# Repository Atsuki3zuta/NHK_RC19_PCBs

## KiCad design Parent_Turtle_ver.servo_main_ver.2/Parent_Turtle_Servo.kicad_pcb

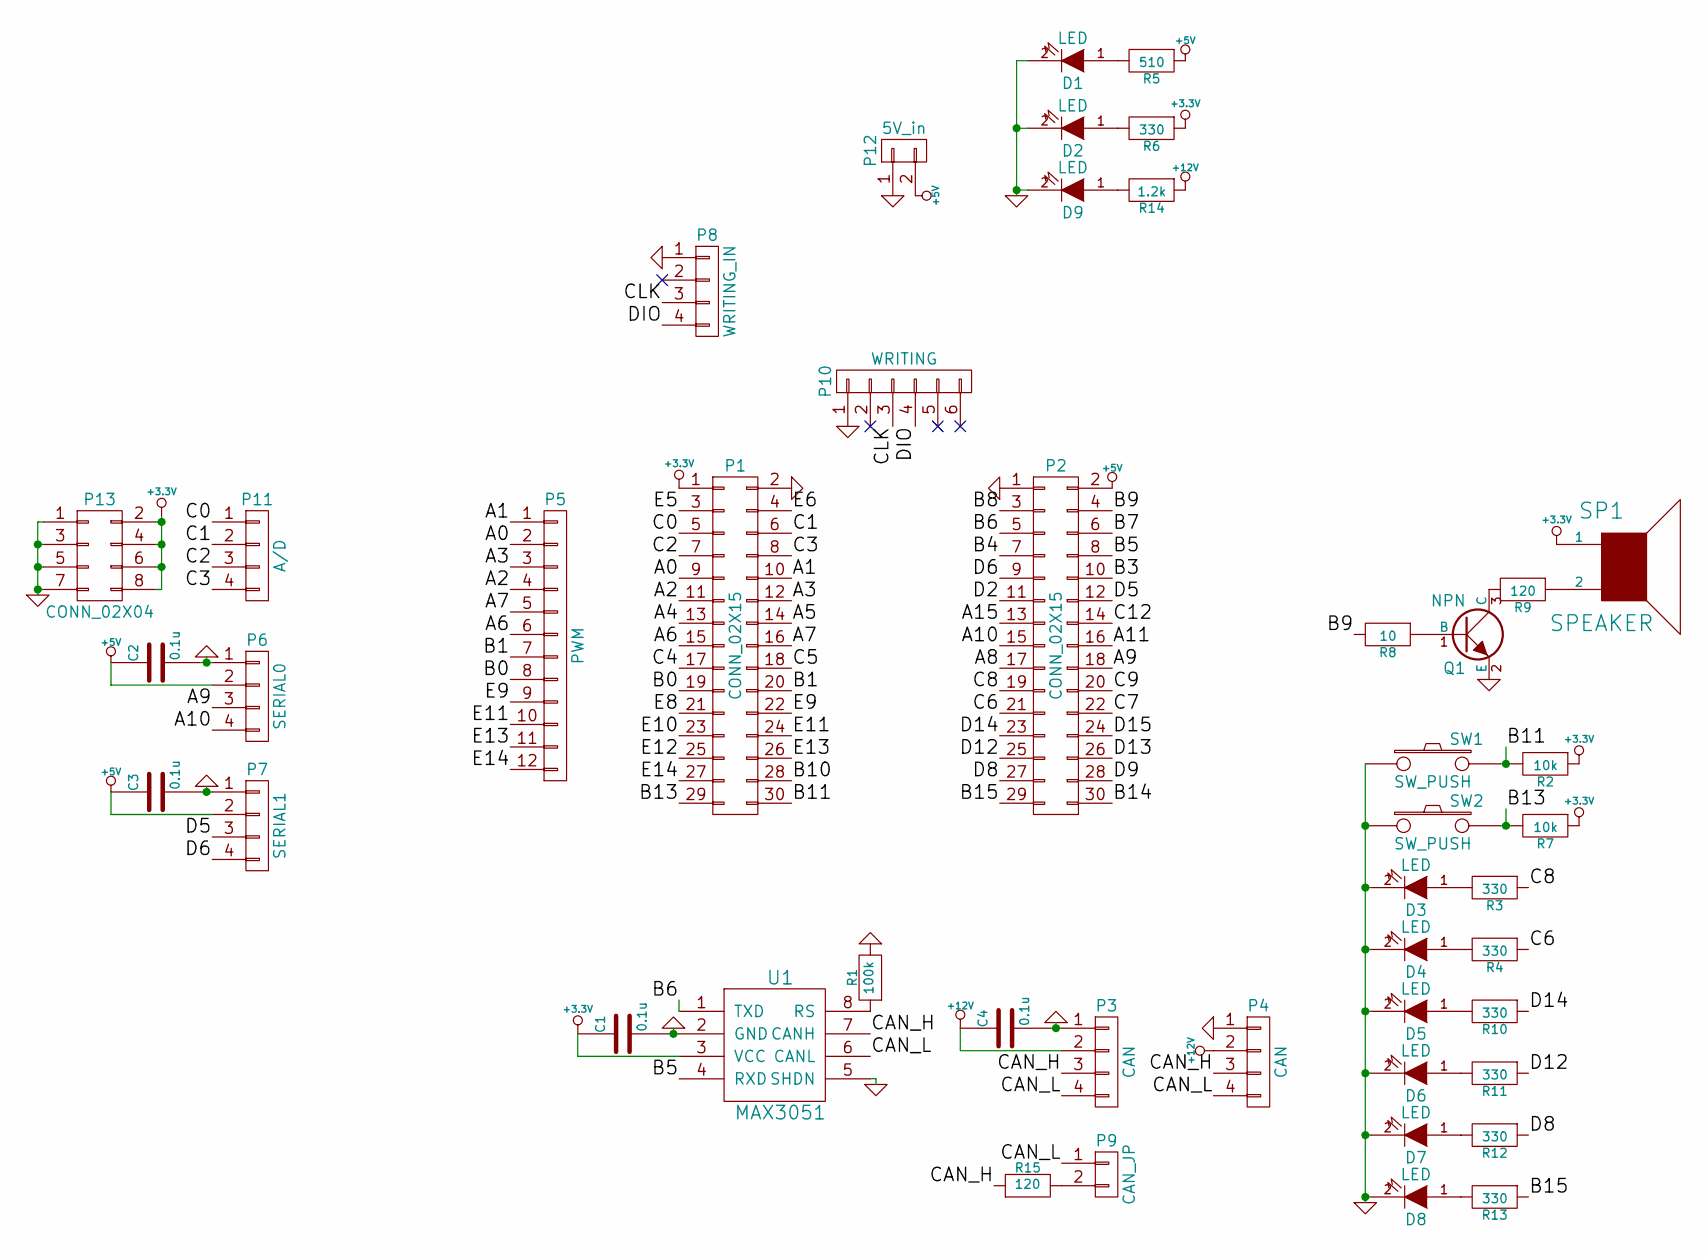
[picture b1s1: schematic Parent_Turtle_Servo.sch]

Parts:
C1, C2, C3, C4: 0.1u; C_0603
D1, D2, D3, D4, D5, D6, D7, D8, D9: LED; LED-3MM
P1, P2: CONN_02X15; Socket_Strip_Straight_2x15
P3: CAN; XA_4T
P4: CAN; XA_4LC
P5: PWM; Pin_Header_Straight_1x12
P6: SERIAL0; XA_4T
P7: SERIAL1; XA_4T
P8: WRITING_IN; XA_4LC
P9: CAN_JP; Pin_Header_Straight_1x02
P10: WRITING; Socket_Strip_Straight_1x06
P11: A/D; Pin_Header_Straight_1x04
P12: 5V_in; XA_2T
P13: CONN_02X04; Pin_Header_Straight_2x04
Q1: NPN; SOT-23
R1: 100k; R_0603
R2, R7: 10k; R_0603
R3, R4, R6, R10, R11, R12, R13: 330; R_0603
R5: 510; R_0603
R8: 10; R_0603
R9, R15: 120; R_0603
R14: 1.2k; R_0603
SP1: SPEAKER; UGCT7525AN4
SW1, SW2: SW_PUSH; SW_PUSH_6mm
U1: MAX3051; SOIC-8_3.9x4.9mm_Pitch1.27mm

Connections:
+3.3V: C1.1, P1.1, P13.2, P13.4, P13.6, P13.8, R2.1, R6.1, R7.1, SP1.1, U1.3 (VCC)
+5V: C2.1, C3.1, P2.2, P6.2, P7.2, P12.2, R5.1
+12V: C4.1, P3.2, P4.2, R14.1
/A0: P1.9, P5.2
/A1: P1.10, P5.1
/A2: P1.11, P5.4
/A3: P1.12, P5.3
/A4: P1.13
/A5: P1.14
/A6: P1.15, P5.6
/A7: P1.16, P5.5
/A8: P2.17
/A9: P2.18, P6.3
/A10: P2.15, P6.4
/A11: P2.16
/A15: P2.13
/B0: P1.19, P5.8
/B1: P1.20, P5.7
/B3: P2.10
/B4: P2.7
/B5: P2.8, U1.4 (RXD)
/B6: P2.5, U1.1 (TXD)
/B7: P2.6
/B8: P2.3
/B9: P2.4, R8.2
/B10: P1.28
/B11: P1.30, R2.2, SW1.2
/B13: P1.29, R7.2, SW2.2
/B14: P2.30
/B15: P2.29, R13.1
/C0: P1.5, P11.1
/C1: P1.6, P11.2
/C2: P1.7, P11.3
/C3: P1.8, P11.4
/C4: P1.17
/C5: P1.18
/C6: P2.21, R4.1
/C7: P2.22
/C8: P2.19, R3.1
/C9: P2.20
/C12: P2.14
/CAN_H: P3.3, P4.3, R15.1, U1.7 (CANH)
/CAN_L: P3.4, P4.4, P9.1, U1.6 (CANL)
/CLK: P8.3, P10.3
/D2: P2.11
/D5: P2.12, P7.3
/D6: P2.9, P7.4
/D8: P2.27, R12.1
/D9: P2.28
/D12: P2.25, R11.1
/D13: P2.26
/D14: P2.23, R10.1
/D15: P2.24
/DIO: P8.4, P10.4
/E5: P1.3
/E6: P1.4
/E8: P1.21
/E9: P1.22, P5.9
/E10: P1.23
/E11: P1.24, P5.10
/E12: P1.25
/E13: P1.26, P5.11
/E14: P1.27, P5.12
GND: C1.2, C2.2, C3.2, C4.2, D1.2 (K), D2.2 (K), D3.2 (K), D4.2 (K), D5.2 (K), D6.2 (K), D7.2 (K), D8.2 (K), D9.2 (K), P1.2, P2.1, P3.1, P4.1, P6.1, P7.1, P8.1, P10.1, P12.1, P13.1, P13.3, P13.5, P13.7, Q1.2 (E), R1.2, SW1.1, SW2.1, U1.2 (GND), U1.5 (SHDN)
unnamed: D1.1 (A), R5.2
unnamed: D2.1 (A), R6.2
unnamed: D3.1 (A), R3.2
unnamed: D4.1 (A), R4.2
unnamed: D5.1 (A), R10.2
unnamed: D6.1 (A), R11.2
unnamed: D7.1 (A), R12.2
unnamed: D8.1 (A), R13.2
unnamed: D9.1 (A), R14.2
unnamed: P9.2, R15.2
unnamed: Q1.1 (B), R8.1
unnamed: Q1.3 (C), R9.2
unnamed: R1.1, U1.8 (RS)
unnamed: R9.1, SP1.2

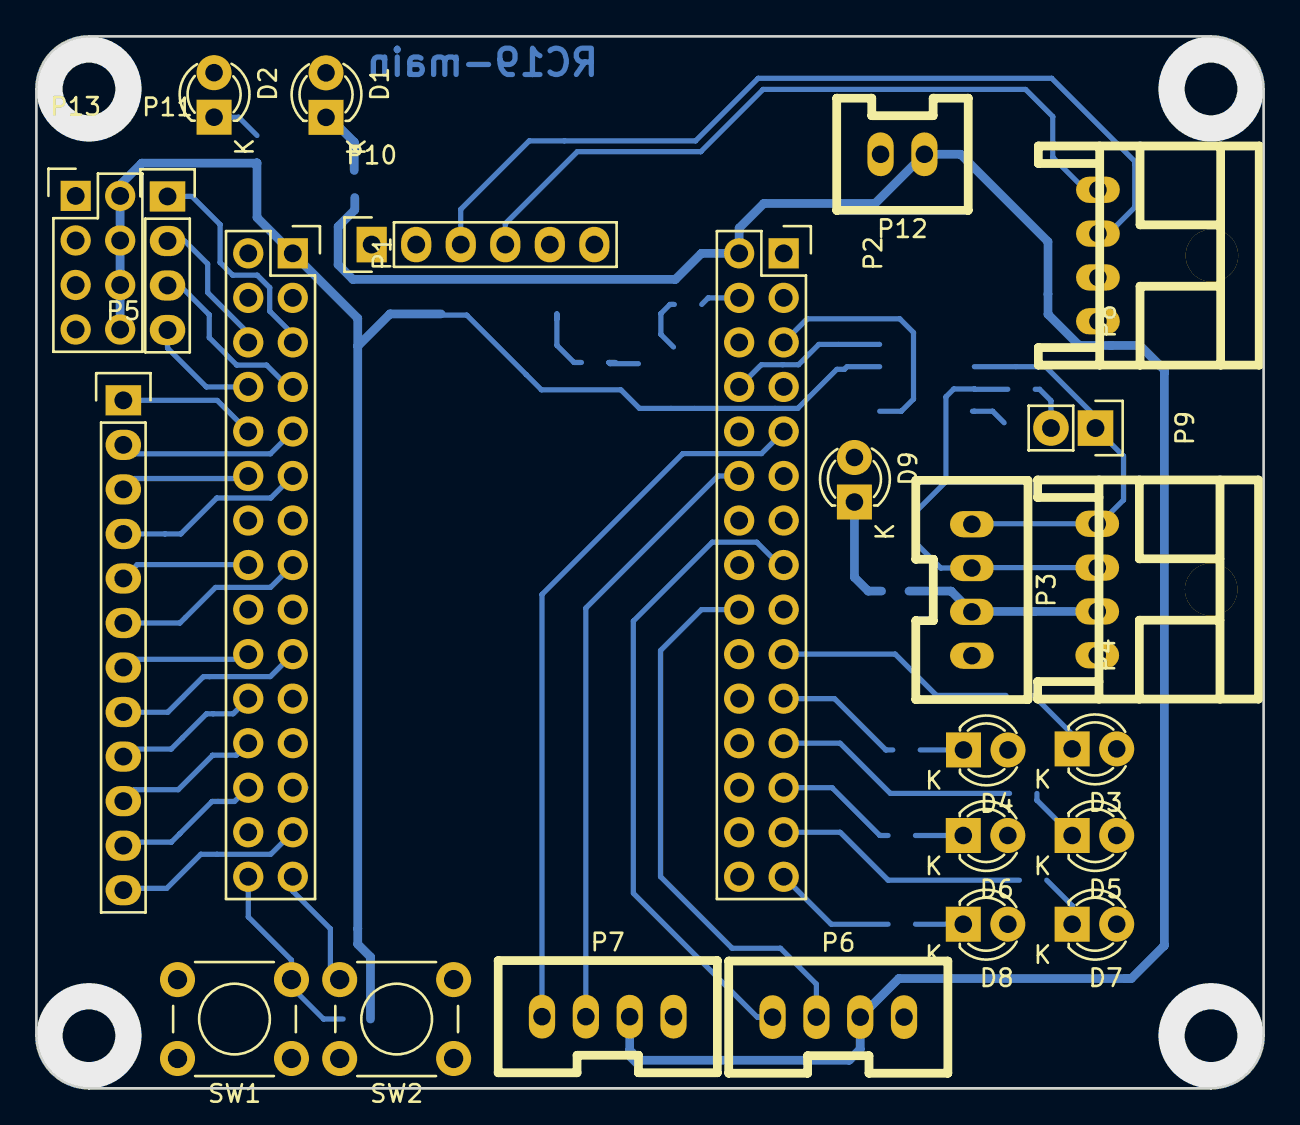
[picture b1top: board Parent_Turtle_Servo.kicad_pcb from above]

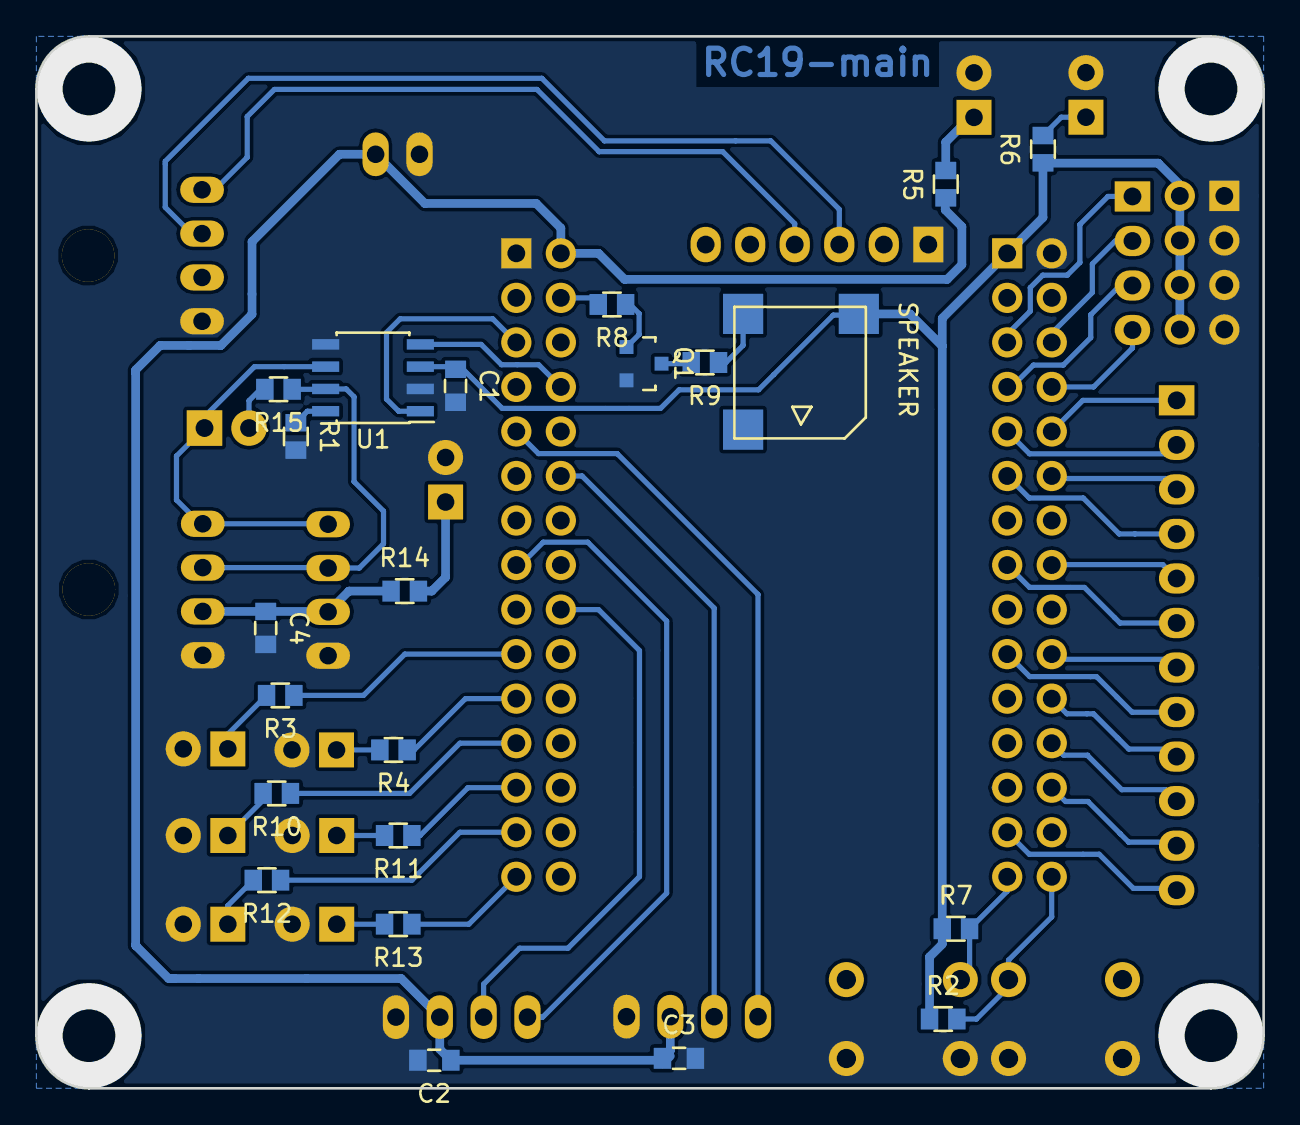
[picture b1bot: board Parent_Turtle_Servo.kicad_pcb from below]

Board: 2 copper layers, 70.0 x 60.0 mm, 46 parts (22 on the bottom side), 53 nets.

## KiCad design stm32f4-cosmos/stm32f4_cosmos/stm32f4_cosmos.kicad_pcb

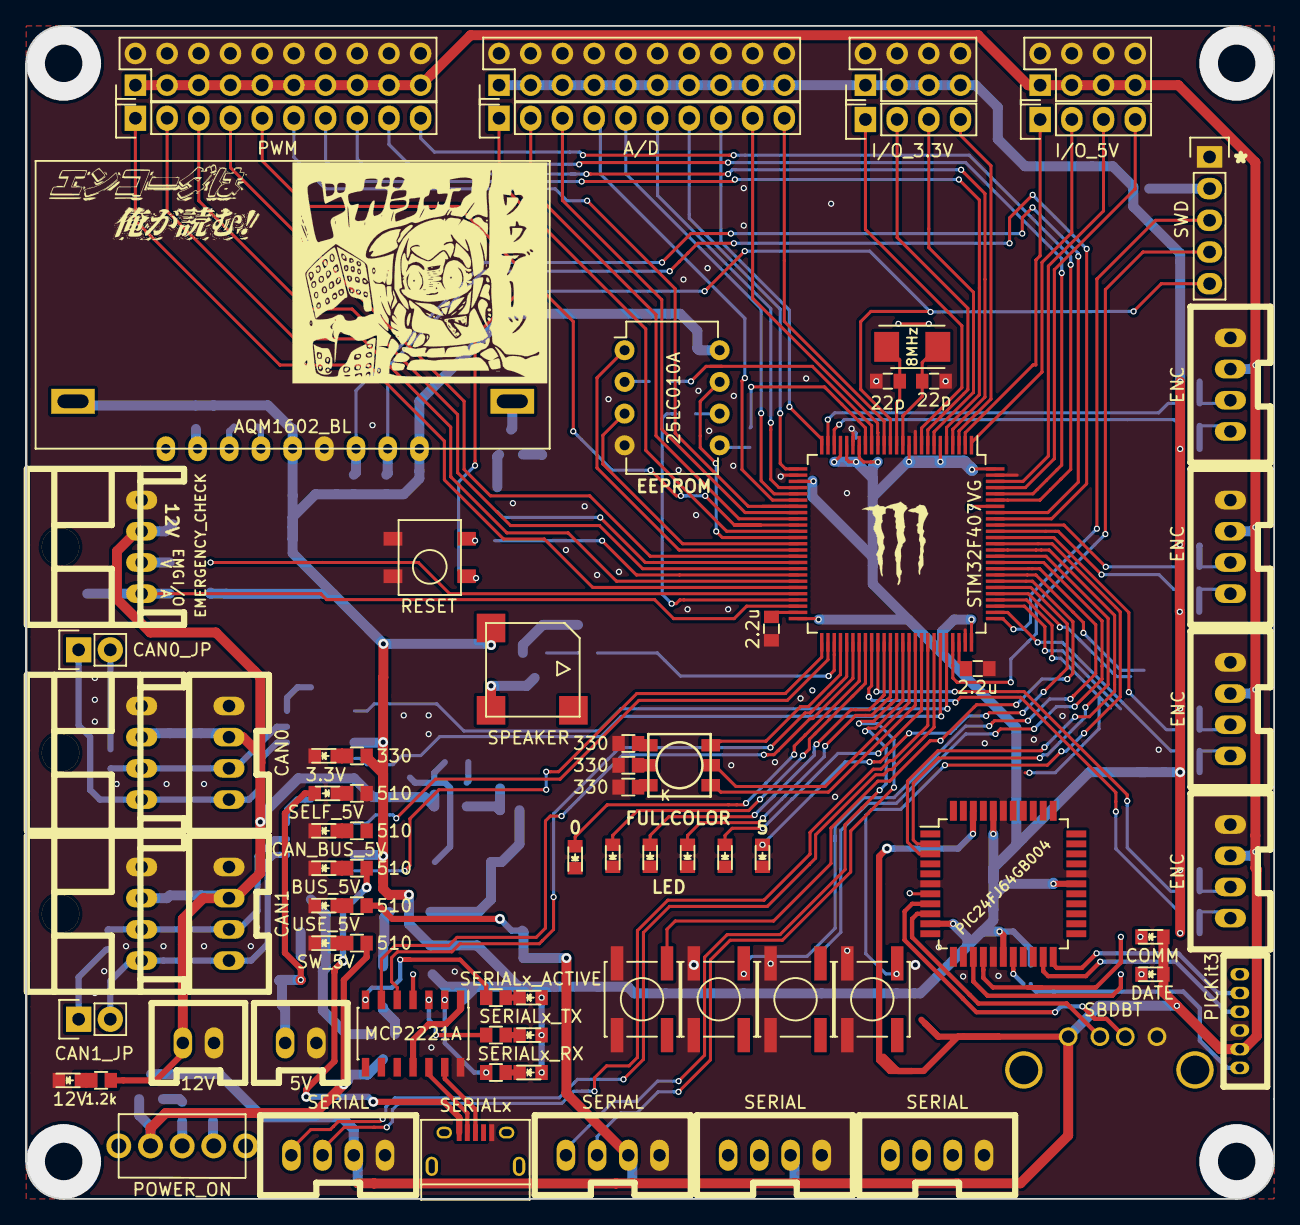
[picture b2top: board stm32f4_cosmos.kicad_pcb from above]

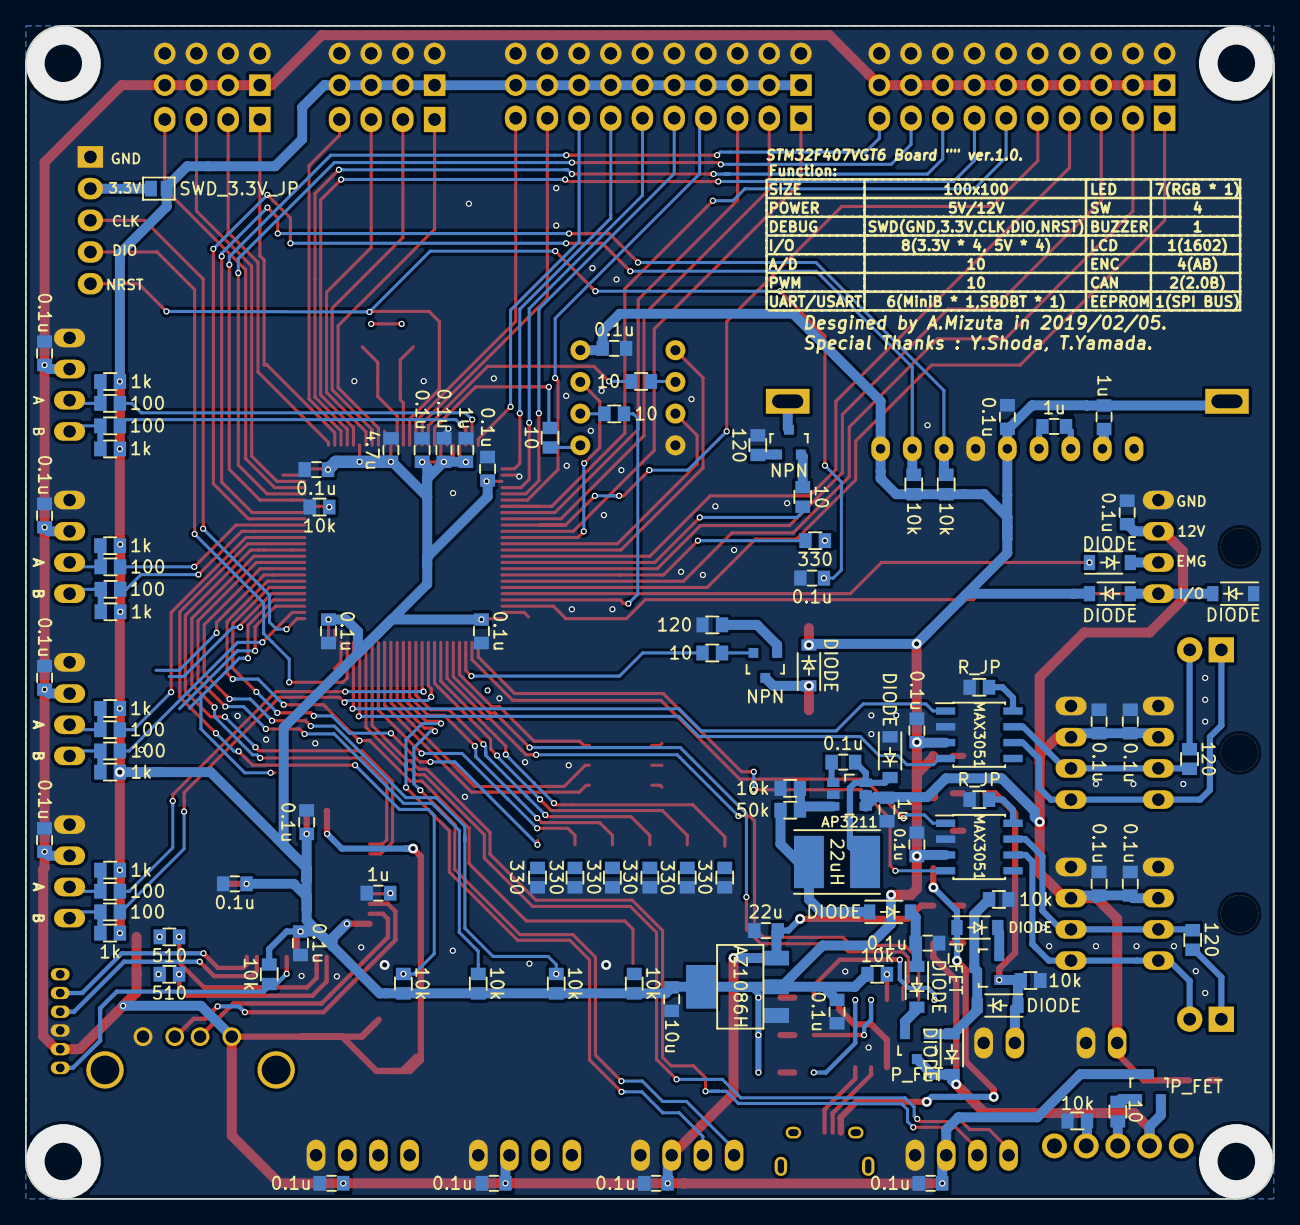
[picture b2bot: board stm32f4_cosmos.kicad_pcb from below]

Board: 2 copper layers, 100.0 x 94.0 mm, 192 parts (111 on the bottom side), 170 nets.

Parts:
C1, C19, C29, C30, C34: 1u; C_0603
C2, C3, C4, C5, C8, C9, C10, C12, C14, C15, C16, C17, C18, C20, C21, C22, C23, C24, C25, C28, C31, C32, C33, C36, C37, C38, C39, C40, C41, C42: 0.1u; C_0603
C6: 22u; C_0603
C7: 10u; C_0603
C11, C13: 22p; C_0603
C26, C27: 2.2u; C_0603
C35: 4.7u; C_0603
D1: DATE; LED_0603
D2: COMM; LED_0603
D3: SERIALx_RX; LED_0603
D4: SERIALx_TX; LED_0603
D5: SERIALx_ACTIVE; LED_0603
D6: SELF_5V; LED_0603
D7: BUS_5V; LED_0603
D8: CAN_BUS_5V; LED_0603
D9: SW_5V; LED_0603
D10: USE_5V; LED_0603
D11: 3.3V; LED_0603
D12, D13, D14, D15, D16, D17, D20, D26, D27, D28: DIODE; SOD-123
D18: 12V; LED_0603
D19, D21, D22, D23, D24, D25: LED; LED_0603
IC1: PIC24FJ64GB004; LQFP-44_10x10mm_Pitch0.8mm
JP1: CAN0_JP; Pin_Header_Straight_1x02
JP2: CAN1_JP; Pin_Header_Straight_1x02
JP3: SWD_3.3V_JP; GS2
L1: 22uH; Inductor_Taiyo-Yuden_NR-50xx_HandSoldering
LED1: RESET; TSHD
P1: PICKit3; ZH_6T
P2: SBDBT; USB_A
P3, P4, P6, P7: ENC; XA_4T
P5: SERIALx; USB_Micro-B
P8, P9, P15, P16: SERIAL; XA_4T
P10: 5V; XA_2T
P11: CAN0; XA_4T
P12: CAN1; XA_4T
P13: CAN0; XA_4LC
P14: CAN1; XA_4LC
P17: 12V; XA_2T
P18: SWD; Pin_Header_Straight_1x05
P23: A/D; Pin_Header_Straight_1x10
P24: PWM; Pin_Header_Straight_1x10
P25: A/D_batt; Pin_Header_Straight_2x10
P26: PWM_batt; Pin_Header_Straight_2x10
P27: EMERGENCY_CHECK; XA_4LC
P28: I/O_3.3V; Pin_Header_Straight_1x04
P29: I/O_5V; Pin_Header_Straight_1x04
P30: I/O_3.3V_batt; Pin_Header_Straight_2x04
P31: I/O_5V_batt; Pin_Header_Straight_2x04
Q1, Q2, Q3: P_FET; SOT-23
Q4, Q5: NPN; SOT-123
R1, R12, R25, R32, R33, R36, R37, R45, R50, R52, R54, R55, R56: 10k; R_0603
R2, R3, R26, R27, R28, R29, R30: 510; R_0603
R4, R5, R6, R7, R13, R14, R15, R16: 100; R_0603
R8, R9, R10, R11, R18, R19, R20, R21: 1k; R_0603
R17, R22, R23, R24, R31, R46, R47, R48, R49, R57, R58, R59, R60, R61: 330; R_0603
R34, R42, R51, R62, R63, R64: 10; R_0603
R35: 50k; R_0603
R38, R39: R_JP; R_0603
R40, R41, R43, R53: 120; R_0603
R44: 1.2k; R_0603
SP1: SPEAKER; UGCT7525AN4
SW1: POWER_ON; 2MS1-T1-B4-VS2-Q-E
SW2: SW1; SW_SPST_EVPBF
SW3: SW0; SW_SPST_EVPBF
SW4: SW2; SW_SPST_EVPBF
SW5: SW3; SW_SPST_EVPBF
U1: STM32F407VG; LQFP-100_14x14mm_Pitch0.5mm
U2: AZ1086H
U3: MCP2221A; SOIC-14_3.9x8.7mm_Pitch1.27mm
U4: AP3211; TSOT-6-MK06A
U5, U6: MAX3051; SOIC-8_3.9x4.9mm_Pitch1.27mm
U7: AQM1602_BL; AQM1602_BL_Fad
U8: OSTBABS4C2B
U9: LOGO; Mini_Monster
U10: LOGO; kitLogo_Mask_5.0x5.0
U11: LOGO; PPTP_uva_silk_20x18
U12: 25LC010A; DIP-8_W7.62mm
U13: LOGO; Enc_19.3x7.0_silk
X1: 8MHz; Crystal_SMD_5032_2Pads

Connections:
+3.3V: C2.2, C3.2, C4.2, C7.1, C10.1, C20.2, C21.2, C28.2, C29.2, C33.2, C34.2, C35.2, C36.2, C37.2, C38.2, C39.2, C40.2, C41.2, D3.1, D4.1, D5.1, D20.2, D27.2, IC1.10, IC1.17, IC1.28, IC1.40, JP3.1, P25.1, P25.3, P25.5, P25.7, P25.9, P25.11, P25.13, P25.15, P25.17, P25.19, P30.1, P30.3, P30.5, P30.7, R1.2, R8.2, R9.2, R10.2, R11.2, R12.2, R18.2, R19.2, R20.2, R21.2, R31.2, R45.1, R50.1, R52.1, R54.1, R55.1, R56.1, SP1.1, U1.6, U1.11, U1.19, U1.21, U1.22, U1.28, U1.50, U1.75, U1.100, U2.2, U3.1, U3.11, U5.3, U6.3, U7.5, U7.9, U7.10, U12.8
+5C: D16.2, Q2.2, Q3.3, R29.2, SW1.1
+5V: C6.1, C8.2, C9.2, C14.2, C15.2, C16.2, C17.2, C24.2, C25.2, D1.1, D2.1, IC1.42, P1.2, P2.1, P3.2, P4.2, P6.2, P7.2, P8.2, P9.2, P15.2, P16.2, P26.1, P26.3, P26.5, P26.7, P26.9, P26.11, P26.13, P26.15, P26.17, P26.19, P31.1, P31.3, P31.5, P31.7, Q2.3, R30.2, U2.3
+12V: C19.1, C22.2, C23.2, C31.2, C32.2, C42.2, P11.2, P12.2, P13.2, P14.2, P17.2, P27.2, R44.2, U4.4, U4.5
/5V: D12.2, D16.1, Q1.3, Q3.1, R37.1
/ADC12_IN2: P23.8, U1.25
/ADC12_IN3: P23.7, U1.26
/ADC12_IN4: P23.6, U1.29
/ADC12_IN5: P23.5, U1.30
/ADC12_IN6: P23.4, U1.31
/ADC12_IN9: P23.1, U1.36
/ADC12_IN10: P23.10, U1.15
/ADC12_IN11: P23.9, U1.16
/ADC12_IN14: P23.3, U1.33
/ADC12_IN15: P23.2, U1.34
/BUS_5V: D13.1, P5.1, R27.2
/CAN0_H: P11.3, P13.3, R40.1, U5.7
/CAN0_L: JP1.1, P11.4, P13.4, U5.6
/CAN1_H: P12.3, P14.3, R41.2, U6.7
/CAN1_L: JP2.2, P12.4, P14.4, U6.6
/CAN1_RX: U1.70, U5.4
/CAN1_TX: U1.71, U5.1
/CAN2_RX: U1.51, U6.4
/CAN2_TX: U1.52, U6.1
/CAN_BUS_5V: C5.1, D15.2, D17.1, R28.2
/D+: IC1.8, P2.3
/D+_USB: P5.3, U3.13
/D-: IC1.9, P2.2
/D-_USB: P5.2, U3.12
/FB: R35.2, R36.1, U4.3
/GP0: R22.2, U3.2
/GP1: R23.2, U3.3
/GP2: R24.2, U3.7
/I2C1_SCL: R52.2, U1.92, U7.8
/I2C1_SDA: R50.2, U1.93, U7.7
/MCLR: IC1.18, P1.1, R1.1
/NRST: C12.1, LED1.1, P18.5, U1.14
/OSC_IN: C13.1, U1.12, X1.2
/OSC_OUT: C11.1, U1.13, X1.1
/PA8: D23.1, U1.67
/PB2: U1.37, U12.7
/PB11: D27.1, D28.2, P27.4, U1.48
/PC13: P28.3, U1.7
/PC14: P28.2, U1.8
/PC15: P28.1, U1.9
/PD0: D25.1, U1.81
/PD1: R54.2, SW3.2, U1.82
/PD3: R45.2, SW2.2, U1.84
/PD4: R55.2, SW4.2, U1.85
/PD7: R56.2, SW5.2, U1.88
/PD10: D19.1, U1.57
/PD11: D21.1, U1.58
/PD14: D22.1, U1.61
/PD15: D24.1, U1.62
/PE0: P29.4, U1.97
/PE1: P29.3, U1.98
/PE2: P29.2, U1.1
/PE3: P29.1, U1.2
/PE4: P28.4, U1.3
/PE7: U1.38, U12.3
/PE8: U1.39, U12.1
/PE10: R42.2, U1.41
/PE12: R17.1, U1.43
/PE15: D26.1, U1.46
/PGEC1: IC1.22, P1.5
/PGED1: IC1.21, P1.4
/SPI2_MISO: R62.2, U1.17
/SPI2_MOSI: R64.1, U1.18
/SPI2_SCK: R63.1, U1.47
/SWCLK: P18.3, U1.76
/SWDIO: P18.4, U1.72
/TIM1_CH1: P24.4, U1.40
/TIM1_CH2: P24.3, U1.42
/TIM1_CH3: P24.2, U1.44
/TIM1_CH4: P24.1, U1.45
/TIM2_CH1: R5.2, U1.77
/TIM2_CH2: R4.2, U1.89
/TIM3_CH1: R7.2, U1.90
/TIM3_CH2: R6.2, U1.91
/TIM4_CH1: R16.2, U1.59
/TIM4_CH2: R15.2, U1.60
/TIM5_CH1: R14.2, U1.23
/TIM5_CH2: R13.2, U1.24
/TIM8_CH1: P24.6, U1.32
/TIM8_CH2: P24.5, U1.35
/TIM8_CH3: U1.65, U8.2
/TIM8_CH4: U1.66, U8.1
/TIM9_CH1: P24.8, U1.4
/TIM9_CH2: P24.7, U1.5
/TIM10_CH1: P24.10, U1.95
/TIM11_CH1: P24.9, U1.96
/TIM12_CH1: R51.2, U1.53
/TIM12_CH2: U1.54, U8.3
/UART5_RX: P8.4, U1.83
/UART5_TX: P8.3, U1.80
/USART1_RX: P16.4, U1.69
/USART1_TX: P16.3, U1.68
/USART2_RX: IC1.3, U1.87
/USART2_TX: IC1.2, U1.86
/USART3_RX: U1.56, U3.6
/USART3_TX: U1.55, U3.5
/USART4_RX: P9.4, U1.79
/USART4_TX: P9.3, U1.78
/USART6_RX: P15.4, U1.64
/USART6_TX: P15.3, U1.63
/XA_5V: D6.1, D12.1, P10.2, Q1.1, R33.1
GND: C1.2, C2.1, C3.1, C4.1, C5.2, C6.2, C7.2, C8.1, C9.1, C10.2, C11.2, C12.2, C13.2, C14.1, C15.1, C16.1, C17.1, C19.2, C20.1, C21.1, C22.1, C23.1, C24.1, C25.1, C26.2, C27.2, C28.1, C31.1, C32.1, C33.1, C34.1, C35.1, C36.1, C37.1, C38.1, C39.1, C40.1, C41.1, C42.1, D7.2, D8.2, D9.2, D10.2, D11.2, D14.1, D18.2, D28.1, IC1.6, IC1.16, IC1.29, IC1.39, LED1.2, LED1.4, P1.3, P2.4, P3.1, P4.1, P5.5, P6.1, P7.1, P8.1, P9.1, P10.1, P11.1, P12.1, P13.1, P14.1, P15.1, P16.1, P17.1, P18.1, P25.2, P25.4, P25.6, P25.8, P25.10, P25.12, P25.14, P25.16, P25.18, P25.20, P26.2, P26.4, P26.6, P26.8, P26.10, P26.12, P26.14, P26.16, P26.18, P26.20, P27.1, P30.2, P30.4, P30.6, P30.8, P31.2, P31.4, P31.6, P31.8, R25.2, R26.1, R32.2, R33.2, R36.2, R37.2, R38.1, R39.1, R43.2, R46.1, R47.1, R48.1, R49.2, R53.2, R57.2, R58.2, R59.2, R60.2, R61.2, SW2.1, SW3.1, SW4.1, SW5.1, U1.10, U1.20, U1.27, U1.74, U1.99, U2.1, U3.14, U4.2, U5.2, U6.2, U7.6, U12.4
unnamed: C1.1, IC1.7
unnamed: C18.1, D14.2, L1.1, U4.6
unnamed: C18.2, U4.1
unnamed: C26.1, U1.49
unnamed: C27.1, U1.73
unnamed: C29.1, U7.2
unnamed: C30.1, U7.3
unnamed: C30.2, U7.4
unnamed: D1.2, R2.1
unnamed: D2.2, R3.1
unnamed: D3.2, R22.1
unnamed: D4.2, R23.1
unnamed: D5.2, R24.1
unnamed: D6.2, R26.2
unnamed: D7.1, R27.1
unnamed: D8.1, R28.1
unnamed: D9.1, R29.1
unnamed: D10.1, R30.1
unnamed: D11.1, R31.1
unnamed: D13.2, Q1.2
unnamed: D15.1, L1.2, R35.1
unnamed: D17.2, Q3.2
unnamed: D18.1, R44.1
unnamed: D19.2, R49.1
unnamed: D20.1, Q5.3, SP1.2
unnamed: D21.2, R57.1
unnamed: D22.2, R58.1
unnamed: D23.2, R59.1
unnamed: D24.2, R60.1
unnamed: D25.2, R61.1
unnamed: D26.2, P27.3
unnamed: IC1.14, R2.2
unnamed: IC1.15, R3.2
unnamed: JP1.2, R40.2
unnamed: JP2.1, R41.1
unnamed: JP3.2, P18.2
unnamed: LED1.3, R17.2
unnamed: P3.3, R4.1, R10.1
unnamed: P3.4, R5.1, R8.1
unnamed: P4.3, R6.1, R11.1
unnamed: P4.4, R7.1, R9.1
unnamed: P6.3, R13.1, R20.1
unnamed: P6.4, R14.1, R18.1
unnamed: P7.3, R15.1, R21.1
unnamed: P7.4, R16.1, R19.1
unnamed: Q2.1, R34.1
unnamed: Q4.1, R42.1
unnamed: Q4.2, R43.1
unnamed: Q4.3, U7.11
unnamed: Q5.1, R51.1
unnamed: Q5.2, R53.1
unnamed: R12.1, U3.4
unnamed: R25.1, U1.94
unnamed: R32.1, SW1.3
unnamed: R34.2, SW1.2
unnamed: R38.2, U5.8
unnamed: R39.2, U6.8
unnamed: R46.2, U8.6
unnamed: R47.2, U8.5
unnamed: R48.2, U8.4
unnamed: R62.1, U12.2
unnamed: R63.2, U12.6
unnamed: R64.2, U12.5

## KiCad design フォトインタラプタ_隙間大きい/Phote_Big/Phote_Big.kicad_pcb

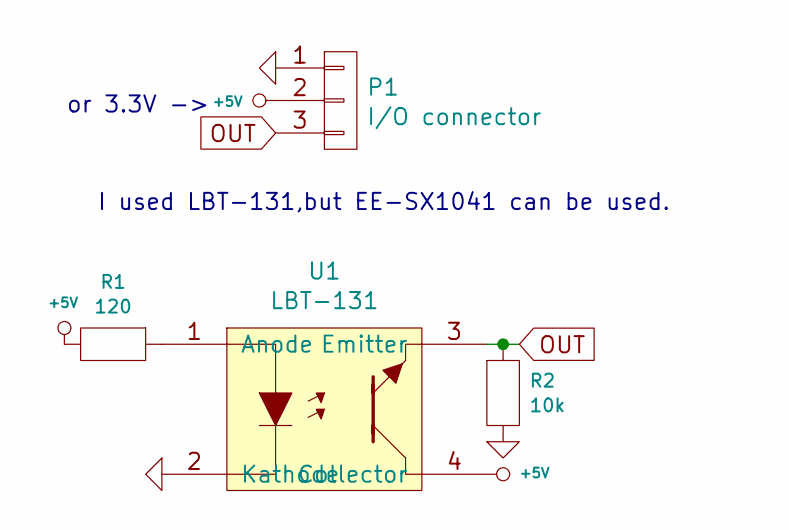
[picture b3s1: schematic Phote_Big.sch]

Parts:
P1: I/O connector; PinHeader_1x03_P2.54mm_Vertical
R1: 120; R_0603_1608Metric_Pad1.05x0.95mm_HandSolder
R2: 10k; R_0603_1608Metric_Pad1.05x0.95mm_HandSolder
U1: LBT-131

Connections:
+5V: P1.2, R1.2, U1.4 (Collector)
GND: P1.1, R2.2, U1.2 (Kathode)
unnamed: R1.1, U1.1 (Anode)
OUT: P1.3, R2.1, U1.3 (Emitter)

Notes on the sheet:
I used LBT-131,but EE-SX1041 can be used.
or 3.3V ->

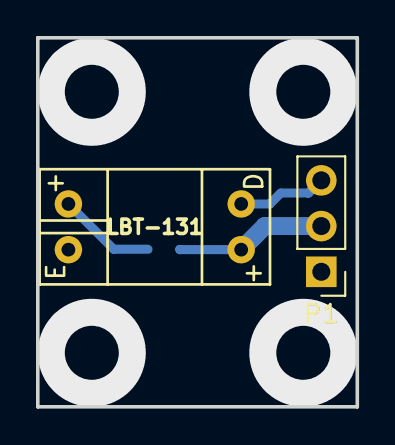
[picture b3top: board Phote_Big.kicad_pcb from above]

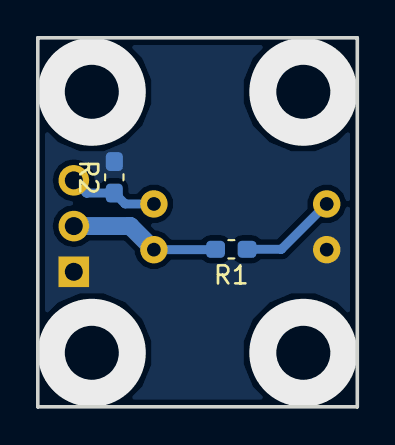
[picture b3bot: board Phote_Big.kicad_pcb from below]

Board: 2 copper layers, 17.8 x 20.5 mm, 4 parts (2 on the bottom side), 4 nets.

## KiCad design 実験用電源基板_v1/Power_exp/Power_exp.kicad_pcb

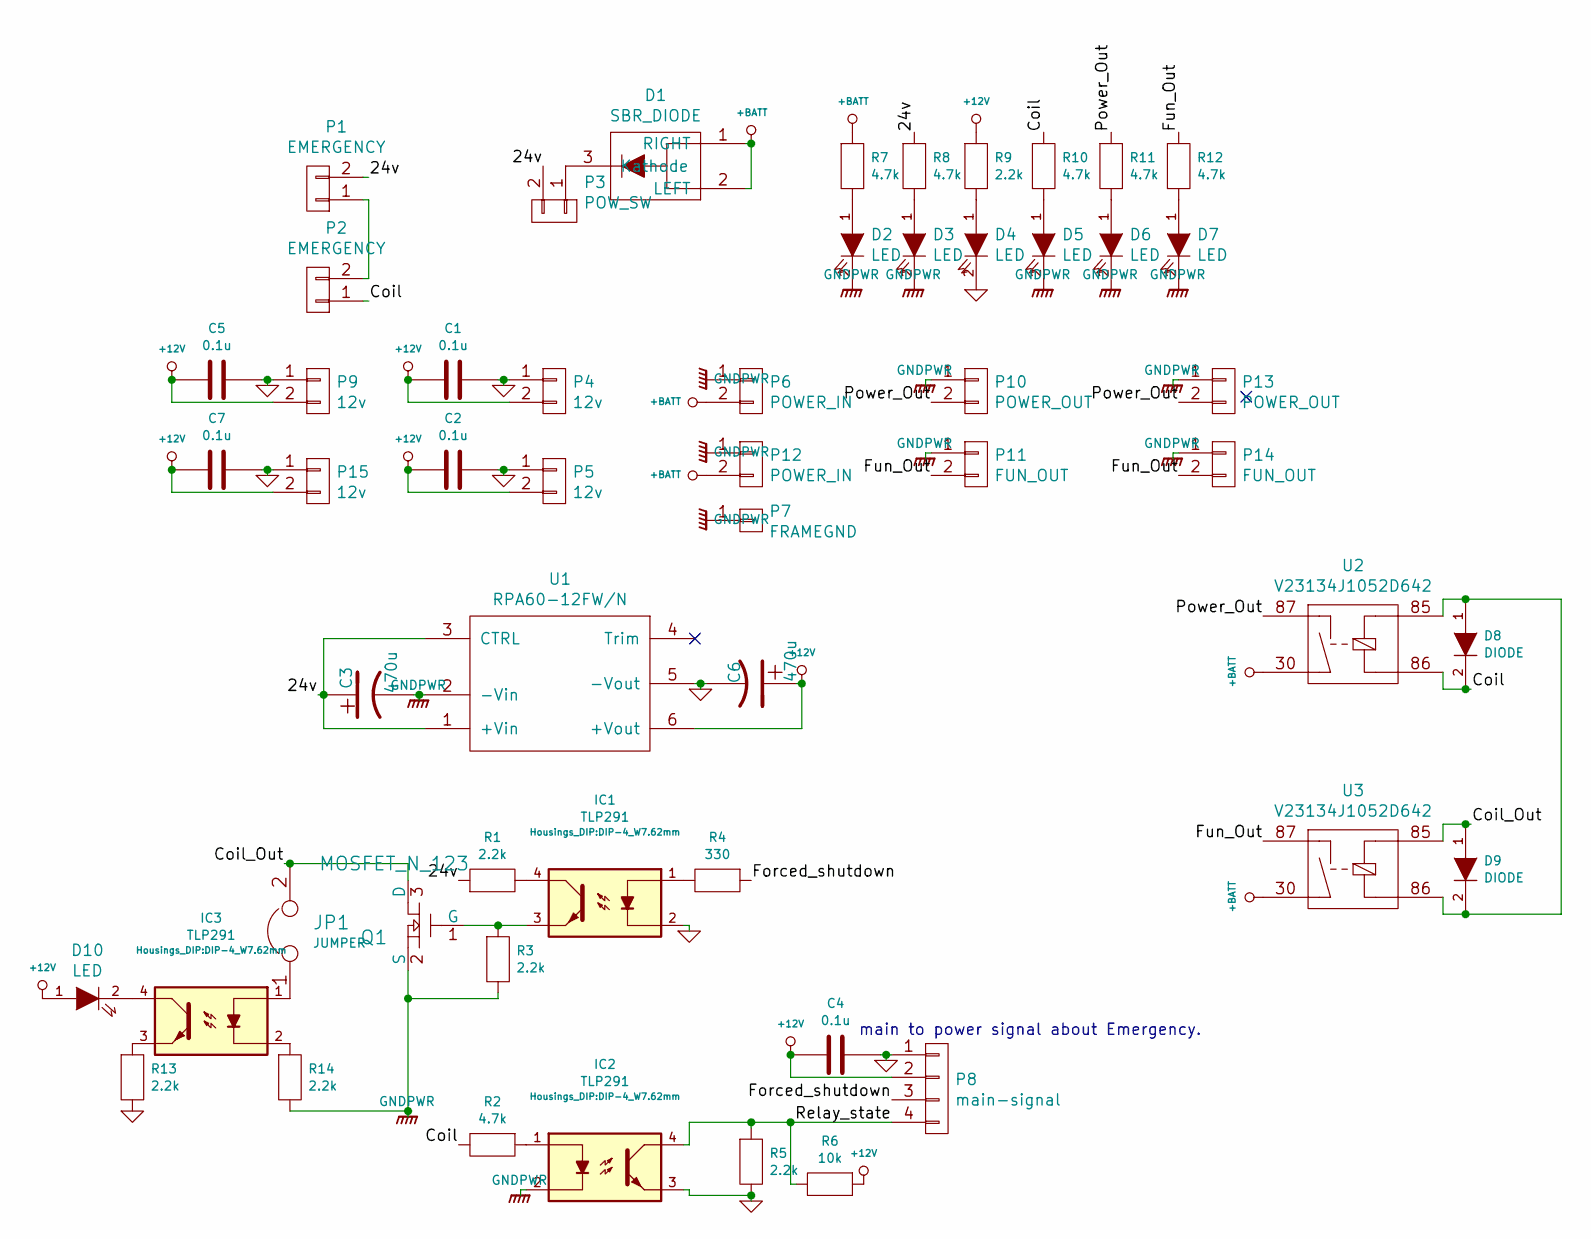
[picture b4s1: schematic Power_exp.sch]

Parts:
C1, C2, C4, C5, C7: 0.1u; C_0603
C3, C6: 470u; C_Radial_D6.3_L11.2_P2.5
D1: SBR_DIODE; TO-277A
D2, D3, D4, D5, D6, D7, D10: LED; LED-3MM
D8, D9: DIODE; SOD-123
IC1, IC2, IC3: TLP291; DIP-4_W7.62mm
JP1: JUMPER; Pin_Header_Straight_1x02
P1, P2: EMERGENCY; XA_2T
P3: POW_SW; XA_2T
P4, P5, P9, P15: 12v; XA_2T
P6, P12: POWER_IN; XT60_T
P7: FRAMEGND; SolderWirePad_single_2mmDrill
P8: main-signal; XA_4LC
P10, P13: POWER_OUT; XT60_T
P11, P14: FUN_OUT; XT60_T
Q1: MOSFET_N_123; SOT-23_Handsoldering
R1, R3, R5, R9, R13, R14: 2.2k; R_0603
R2, R7, R8, R10, R11, R12: 4.7k; R_0603
R4: 330; R_0603
R6: 10k; R_0603
U1: RPA60-12FW/N; RPA60-24xxSFW
U2, U3: V23134J1052D642

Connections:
+12V: C1.1, C2.1, C4.2, C5.1, C6.1, C7.1, D10.1 (A), P4.2, P5.2, P8.2, P9.2, P15.2, R6.1, R9.1, U1.6 (+Vout)
+BATT: D1.1 (RIGHT), D1.2 (LEFT), P6.2, P12.2, R7.1, U2.30, U3.30
/24v: C3.1, P1.2, P3.2, R1.1, R8.1, U1.1 (+Vin), U1.3 (CTRL)
/Coil: D8.2 (K), P2.1, R2.2, R10.1, U2.86
/Coil_Out: D9.1 (A), JP1.2, Q1.3 (D), U3.85
/Forced_shutdown: P8.3, R4.1
/Fun_Out: P11.2, P14.2, R12.1, U3.87
/Power_Out: P10.2, P13.2, R11.1, U2.87
/Relay_state: IC2.4, P8.4, R5.1, R6.2
GND: C1.2, C2.2, C4.1, C5.2, C6.2, C7.2, D4.2 (K), IC1.2, IC2.3, P4.1, P5.1, P8.1, P9.1, P15.1, R5.2, R13.2, U1.5 (-Vout)
GNDPWR: C3.2, D2.2 (K), D3.2 (K), D5.2 (K), D6.2 (K), D7.2 (K), IC2.2, P6.1, P7.1, P10.1, P11.1, P12.1, P13.1, P14.1, Q1.2 (S), R3.2, R14.2, U1.2 (-Vin)
unnamed: D1.3 (Kathode), P3.1
unnamed: D2.1 (A), R7.2
unnamed: D3.1 (A), R8.2
unnamed: D4.1 (A), R9.2
unnamed: D5.1 (A), R10.2
unnamed: D6.1 (A), R11.2
unnamed: D7.1 (A), R12.2
unnamed: D8.1 (A), D9.2 (K), U2.85, U3.86
unnamed: D10.2 (K), IC3.4
unnamed: IC1.1, R4.2
unnamed: IC1.3, Q1.1 (G), R3.1
unnamed: IC1.4, R1.2
unnamed: IC2.1, R2.1
unnamed: IC3.1, JP1.1
unnamed: IC3.2, R14.1
unnamed: IC3.3, R13.1
unnamed: P1.1, P2.2

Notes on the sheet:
main to power signal about Emergency.

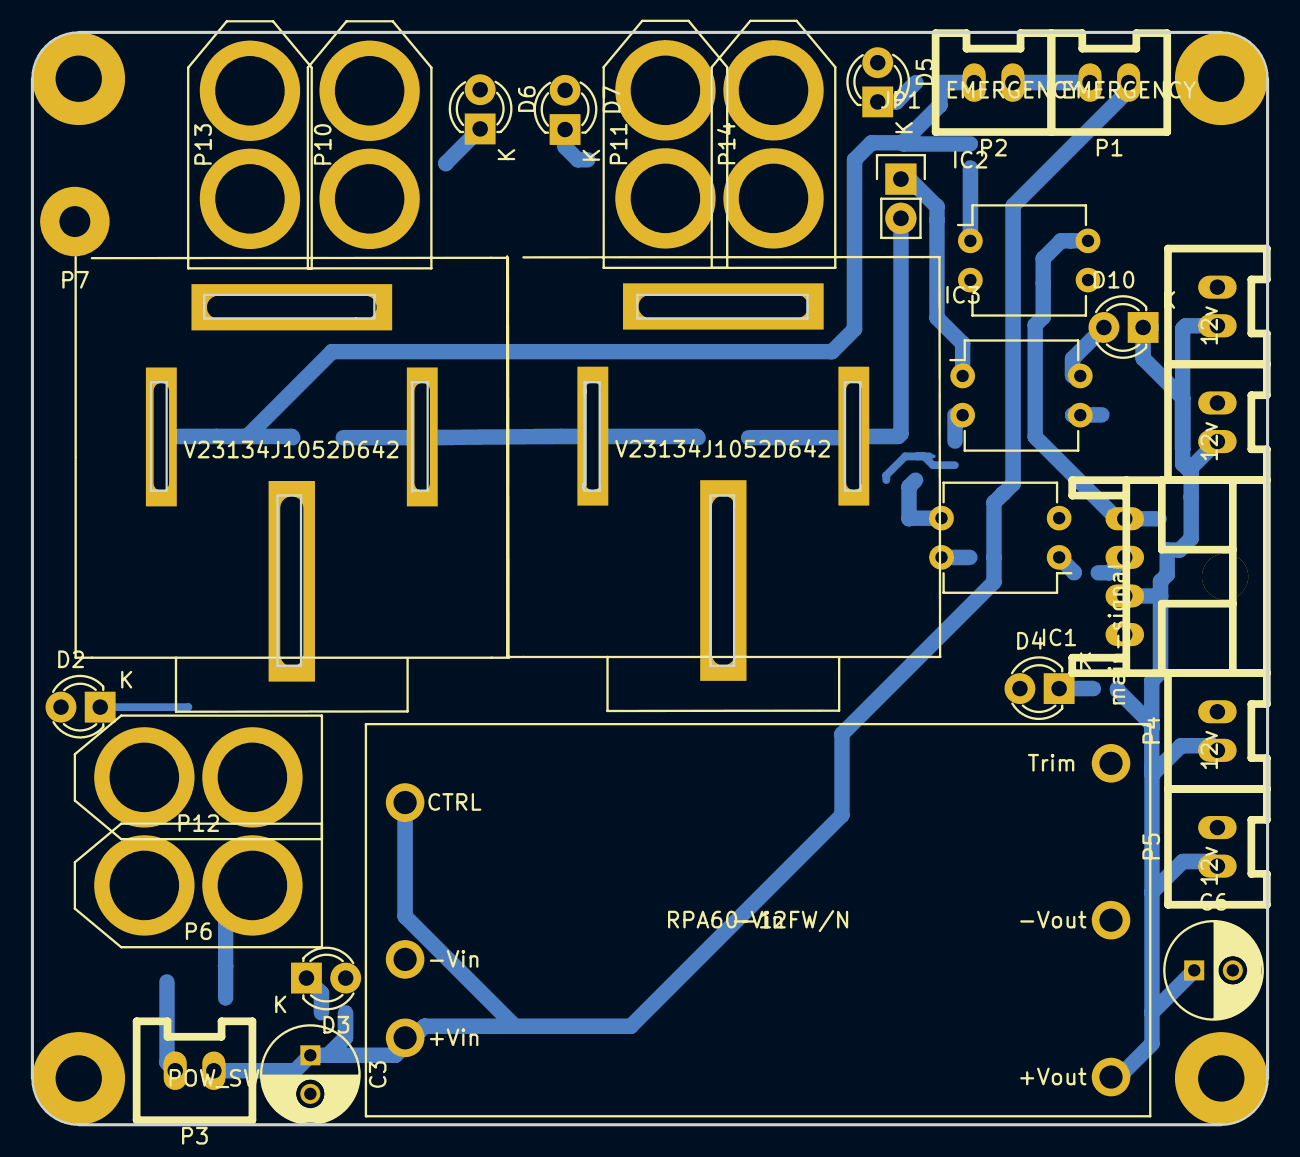
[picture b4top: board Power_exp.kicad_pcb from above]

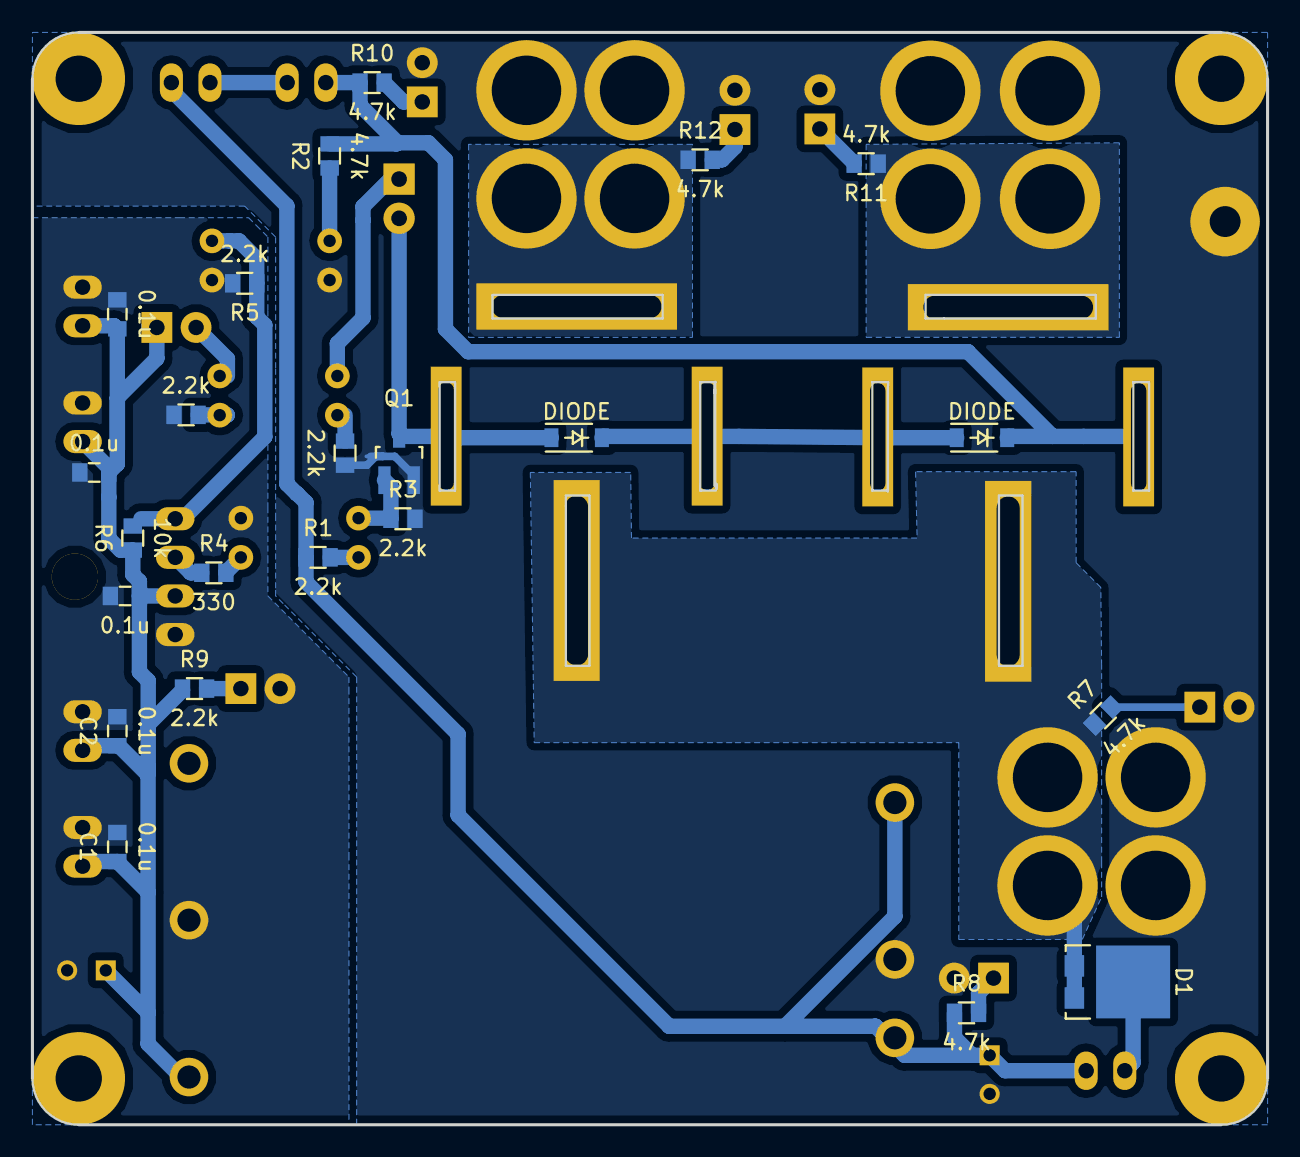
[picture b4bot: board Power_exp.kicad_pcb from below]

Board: 2 copper layers, 80.0 x 70.8 mm, 54 parts (23 on the bottom side), 28 nets.
